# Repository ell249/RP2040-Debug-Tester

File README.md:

## RP2040 Debug Tester
### Licence and design:
-	RP2040 Debug Tester adapted by Elliot Alfirevich http://ell-tech.com/ 
-	Based on Adafruit RP2040 Tester Brains https://github.com/adafruit/RP2040-Based-Tester-Brains-PCB by Adafruit (ladyada & evaherrada) 
-	Licenced under Creative Commons Attribution-ShareAlike 3.0 Unported
-	4-layer impedance controlled circuit board, JLC04161H-7628 to ensure appropriate trace impedance for USB.

### Added features:
1.	USB-Serial converter CP2102N added to snoop serial UART bus, and allow direct serial programming of devices on test using the changeover DPDT switches.
2.	USB Hub with device power reset buttons and USB device current measurement at JP7 using Nordic PPK2 or similar. 
3.	Extra power supply functions added in the FPC 18-pin and external device 0.1in header as JP6.
4.	Additionally JP5 provides connection point for a Nordic PPK2 or similar for measuring load current of external prog-cable devices. “TEST” pin provides opportunity for custom voltages/measured currents. 
5.	Nordic PPK2 can be permanently mounted via the mounting holes and standoffs.

### Notes/changes to Adafruit design:
1.	Dedicated 3.3V regulator provided, in lieu of using the in-built RP2040 buck-boost converter. 
2.	Diode included on 3.3V supply to RP2040 VSYS to prevent back-feeding of ~5V onto the 3.3V bus from plugging in the RP2040 USB port.
3.	USB-C PD controller STUSB4500LQTR ensures enough VBUS current is provided by the host. Previously used 5.1k CC resistor method – but strictly compliant USB hosts would limit supply to 500mA which was not enough.
4.	RTS/DTR logic transistors added for ESP boot/reset to be generated from the CP2102N.
5.	High side switch (Option 1) or separate regulator (Option 2) required to power CP2102N because the CP2102N defaults to pull-up on USB data lines, causing the USB hub to disable the port at start-up (doh!)
6.	USB Hub USB2514B added to enable one cable to the host computer. 
   1.	Port 1 – CP2102N USB-Serial converter
   2.	Port 2 – USB port inc. 1.5A charging
   3.	Port 3 – USB port inc. 500mA power measurement via jumper JP7
   4.	Port 4 – RP2040 via test points.
7.	USB Hub controller strapped to report Port 1 as “non-removable” and enable USB charging support on Port 2.
8.	USB Hub controller requires an external crystal and 1M resistor. Check as newer QFN packages don’t require this resistor.
9.	SD card changed due to part availability. Note new part changes card detect from NO to NC which requires change in Brains library code.
10.	TFT connection not tested. Directly copied from original design.

### Original Adafruit Design
Forked from https://github.com/adafruit/RP2040-Based-Tester-Brains-PCB

This board is what we use internally at Adafruit to program and test boards with microcontrollers on them. 
   * An [RP2040 Pico](https://www.adafruit.com/product/5525) (or perhaps PicoW?) is used to run the test software
   * [Use a 16x2 LCD (ideally RGB backlight)](https://www.adafruit.com/product/398) for display output with color feedback such as green for pass, red for fail. RGB backlight is WS2811-controlled. Don't forget to set the contrast pot on first usage.
   * Serial1 hardware UART has RX/TX pin switch to flip directions
   * 1.9" TFT connector is placed but hasn't been tested or used yet
   * Piezo buzzer can be used for audible feedback alerts
   * STEMMA QT I2C port
   * Big reset button
   * Firmware files can be stored on MicroSD card which is slotted in. 
   * Connect the right hand side, either the 0.1" header or 18-pin EYESPI-like FPC connector to the device-under-test jig which can be different for each product. 
   * [USB Host testing is done with bitbang PIO support in TinyUSB](https://github.com/adafruit/Adafruit_TinyUSB_Arduino), USB 5V power can be turned on / off 
   * Use Philhower RP2040 core for programming
   * The RP2040 brains can perform ESP32 programming, RP2040-via-USB, AVR ICSP/UPDI, or SWD DAP. [See the TestBed library for some examples.](https://github.com/adafruit/Adafruit_TestBed)

### License

Originally designed by Limor Fried/Ladyada for Adafruit Industries. Adafruit invests time and resources providing this open source design, please support Adafruit and open-source hardware by purchasing products from [Adafruit](https://www.adafruit.com)!

Creative Commons Attribution/Share-Alike, all text above must be included in any redistribution. 
See license.txt for additional details.

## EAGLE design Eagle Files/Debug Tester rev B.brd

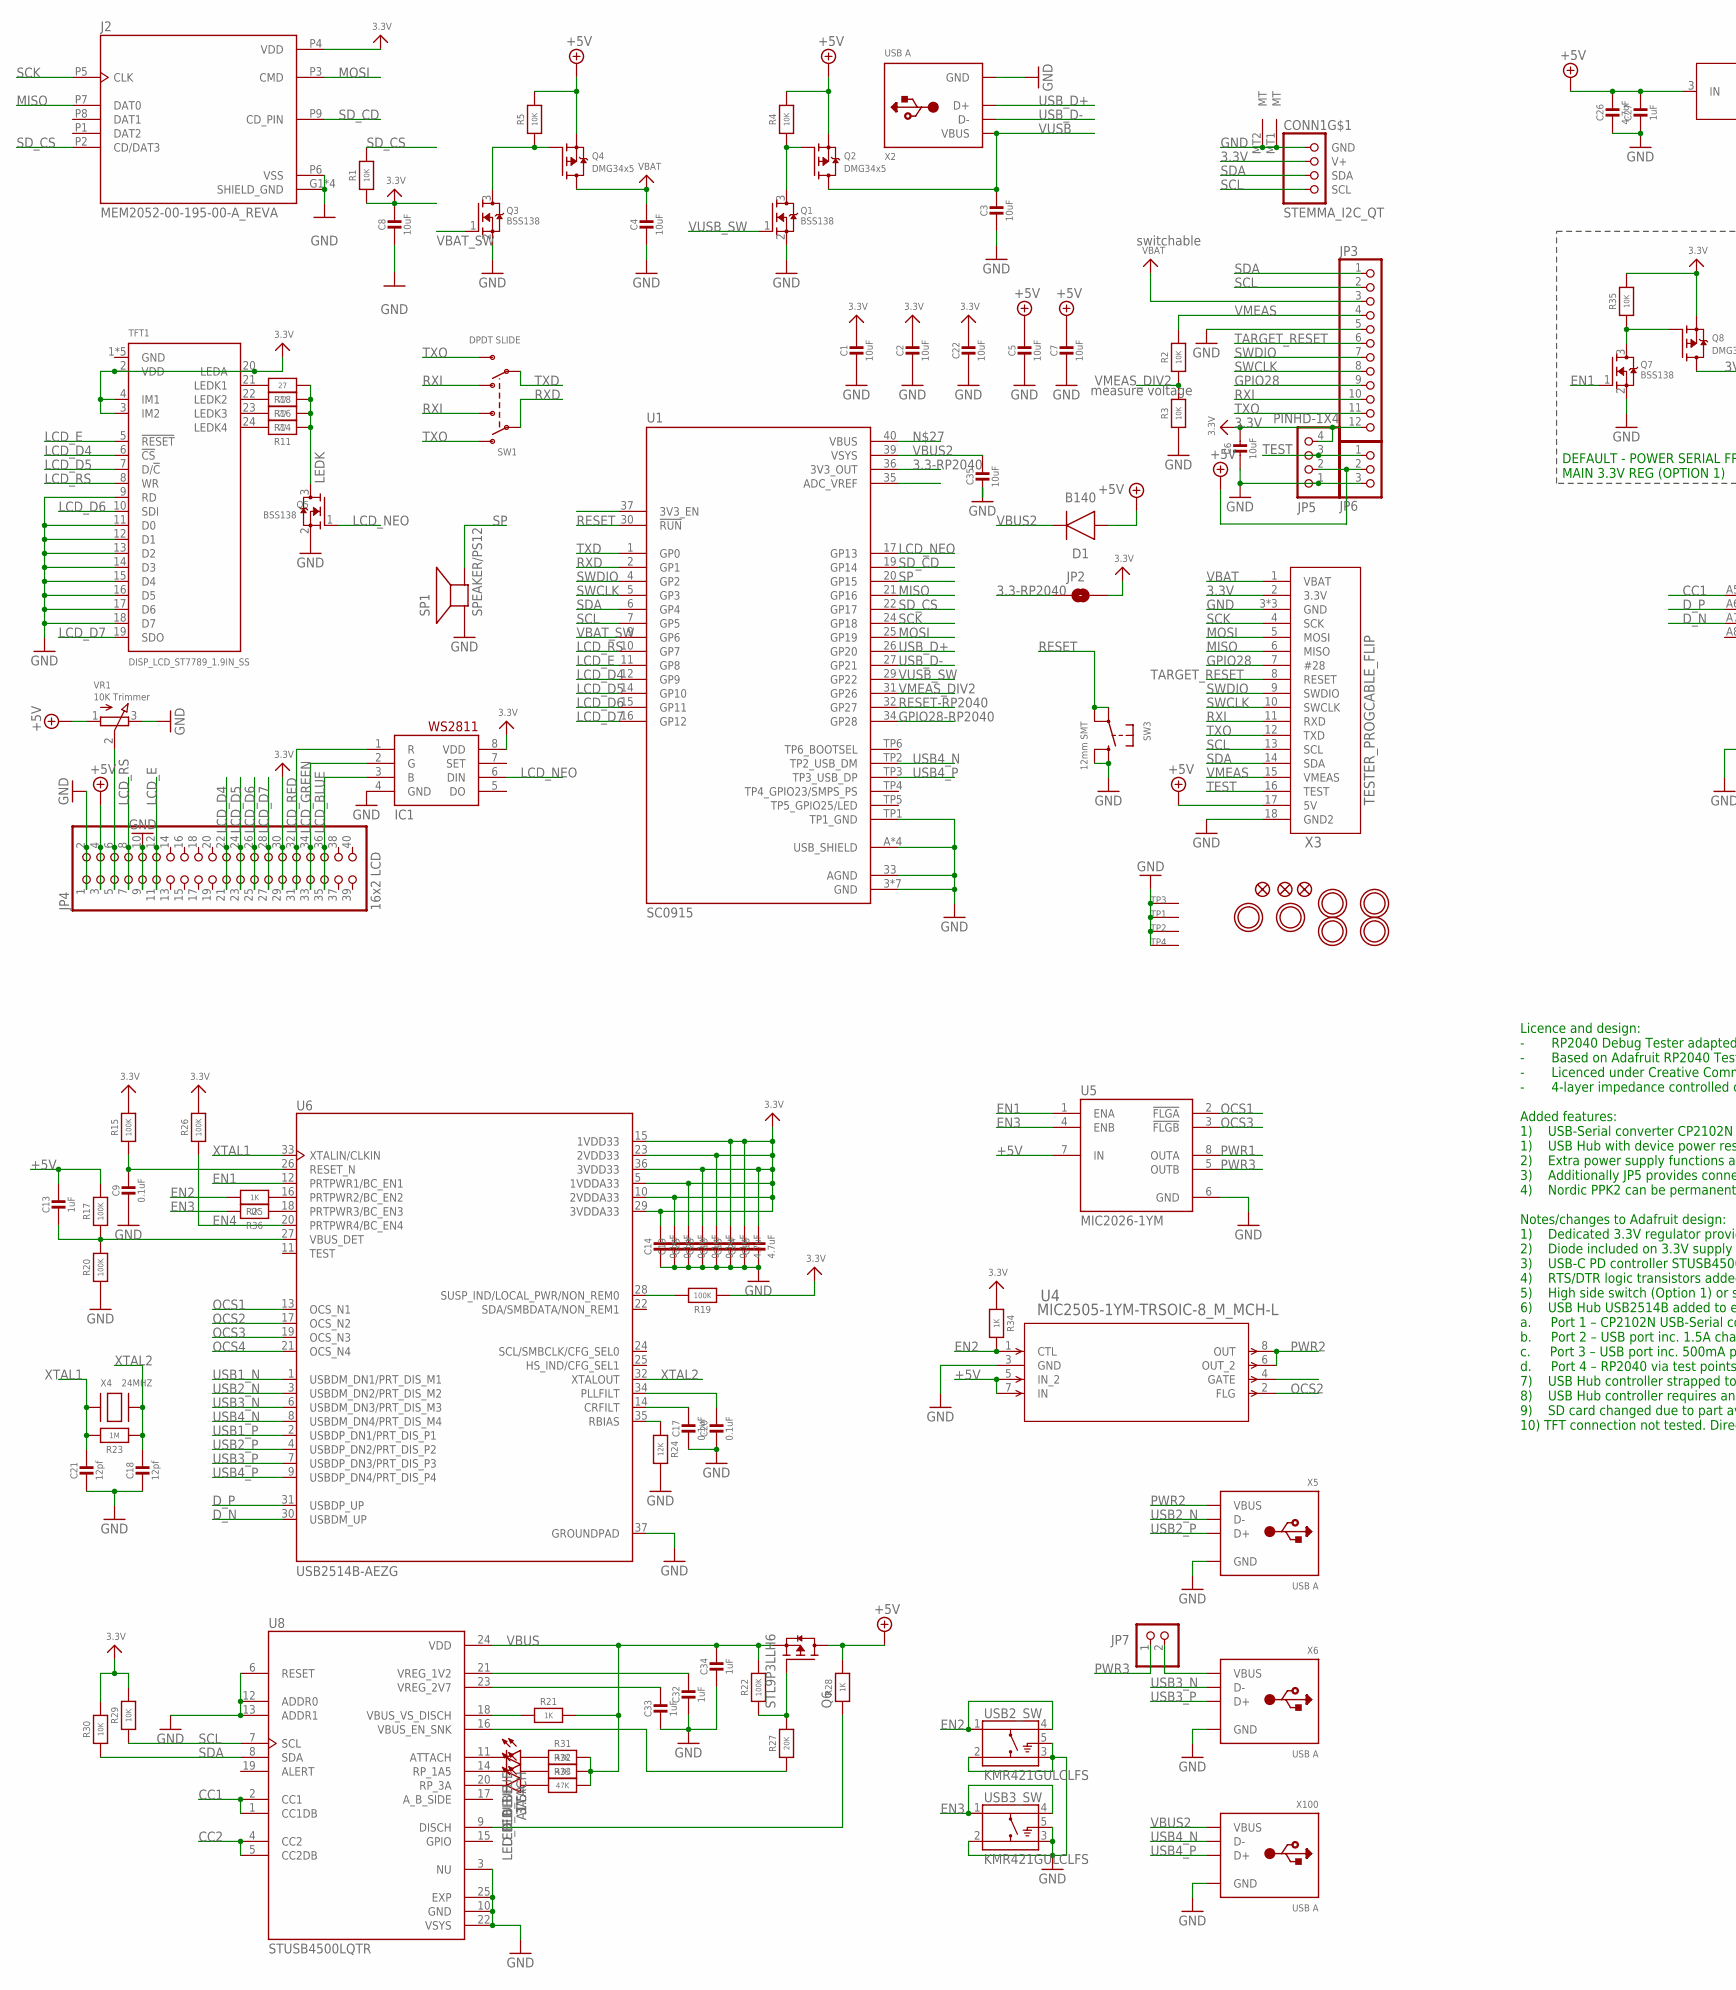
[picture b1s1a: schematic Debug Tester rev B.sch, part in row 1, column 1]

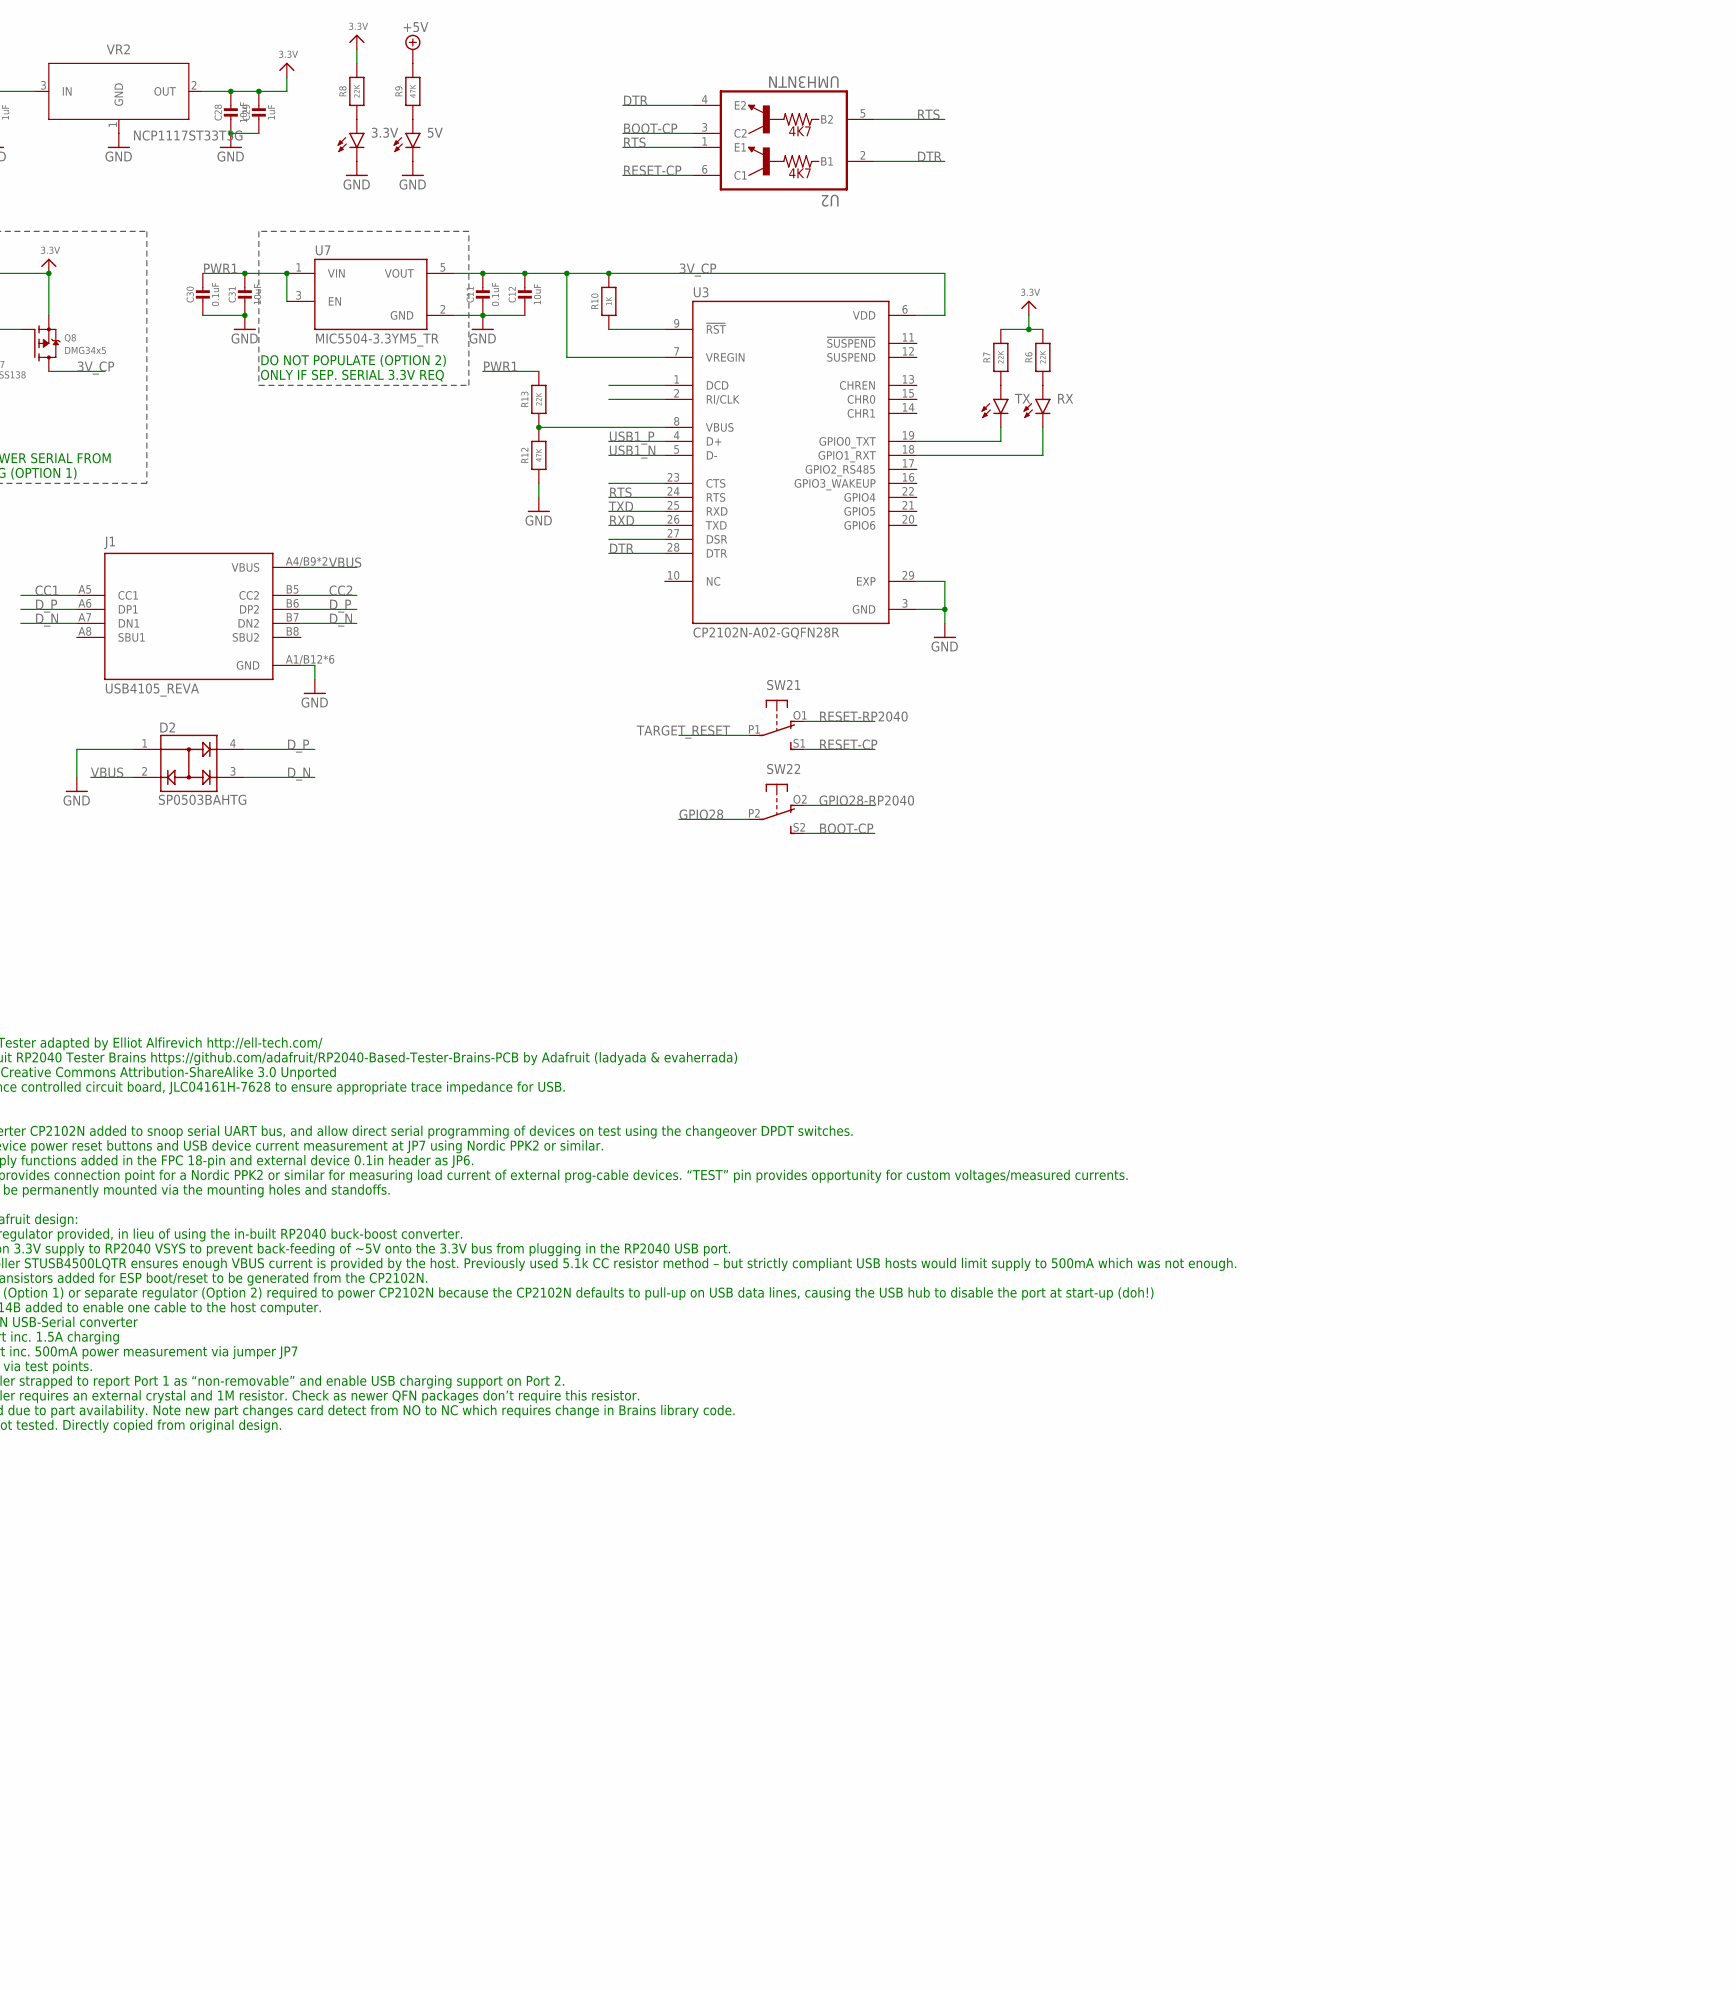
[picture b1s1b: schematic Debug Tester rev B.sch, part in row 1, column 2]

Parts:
1.5A, 3.3V, 3A, 5V: LED_BLUE; LEDC1608X55N_FLAT-B
$$U$1, $$U$2, $$U$3, $$U$5, $$U$6: MOUNTINGHOLE3.0THIN; MOUNTINGHOLE_3.0_PLATEDTHIN
ATTACH: LED_BLUE; LEDC1608X55N_FLAT-B
C1, C2, C3, C4, C5, C6, C7, C8, C12, C22, C28, C31, C35: 10uF; 0603-NO
C9, C10, C11, C14, C15, C17, C19, C20, C23, C25, C30: 0.1uF; 0603-NO
C13, C27, C29, C32, C33, C34: 1uF; 0603-NO
C16, C24, C26: 4.7uF; 0603-NO
C18, C21: 12pf; 0603-NO
CONN1: STEMMA_I2C_QT; JST_SH4
D1: B140; DIOM5226X290N
D2: SP0503BAHTG; SOT143
FID1, FID2, FID3: FIDUCIAL_1MM
IC1: WS2811-SOP8; SO08-SKINNYPADS
J1: USB4105_REVA; GCT_USB4105_REVA
J2: MEM2052-00-195-00-A_REVA; GCT_MEM2052-00-195-00-A_REVA
JP2: JUMPER-SMT_2_NC_PASTE_NO-SILK; SMT-JUMPER_2_NO_NO-SILK
JP3: HEADER-1X12OVAL; 1X12_OVAL
JP4: 16x2 LCD; 2X20_SMT_MALE
JP5: PINHD-1X4; 1X04
JP6: PINHD-1X3/90; 1X03/90
JP7: PINHD-1X2; 1X02
Q1, Q3, Q5, Q7: BSS138; SOT23-WIDE
Q2, Q4, Q8: DMG34x5; SOT23-WIDE
Q6: STL9P3LLH6; TRANS_STL9P3LLH6
R1, R2, R3, R4, R5, R29, R30, R35: 10K; 0603-NO
R6, R7, R8, R13: 22K; 0603-NO
R9, R12, R31, R32, R33: 47K; 0603-NO
R10, R21, R25, R28, R34, R36: 1K; 0603-NO
R11, R14, R16, R18: 27; 0603-NO; LCSC C25190
R15, R17, R19, R20, R22, R26: 100K; 0603-NO
R23: 1M; 0603-NO
R24: 12K; 0603-NO
R27: 20K; 0603-NO
RX: LED_BLUE; LEDC1608X55N_FLAT-B
SP1: SPEAKER/PS12; PS12
SW1: DPDT SLIDE; EG1390; LCSC C318999
SW2: DPDT-EG1390; EG1390
SW3: 12mm SMT; B3F-40XX-SMT
TFT1: DISP_LCD_ST7789_1.9IN_SS; TFT_1.9IN_170X320_30P_SS
TP1, TP2, TP3, TP4: SEWTAP_SMTNUTM3; SMT_NUT_3MM
TX: LED_BLUE; LEDC1608X55N_FLAT-B
U1: SC0915; MODULE_SC0915
U2: UMH3NTN; SOP65P210X100-6N
U3: CP2102N-A02-GQFN28R; IC_CP2102N-A02-GQFN28R
U4: MIC2505-1YM-TRSOIC-8_M_MCH-L; SOIC-8_M_MCH-L
U5: MIC2026-1YM; SOIC127P599X173-8N
U6: USB2514B-AEZG; VQFN50P600X600X100-36N
U7: MIC5504-3.3YM5_TR; SOT95P280X145-5N
U8: STUSB4500LQTR; QFN50P400X400X100-25N
U$7: MOUNTINGHOLE3.0THIN; MOUNTINGHOLE_3.0_PLATEDTHIN
USB2_SW, USB3_SW: KMR421GULCLFS; SW_KMR421GULCLFS
VR1: 10K Trimmer; TRIMPOT_BOURNS_TC33X-2
VR2: NCP1117ST33T3G; SOT230P700X170-4
X2, X5, X6, X100: USB A; USB_HOST-SMT
X3: TESTER_PROGCABLE_FLIP; FPC_0.5MM_18PIN
X4: 24MHZ; NX5032

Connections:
3.3-RP2040: JP2.1, U1.36 (3V3_OUT)
3.3V: C1.1, C2.1, C6.1, C8.1, C10.1, C14.1, C15.1, C16.1, C19.1, C22.1, C23.1, C24.1, C25.1, C28.1, C29.1, CONN1.2 (V+), IC1.8 (VDD), J2.P4 (VDD), JP2.2, JP3.12, JP4.29, JP4.30, JP5.4, Q8.2 (S), R1.1, R6.2, R7.2, R8.2, R15.2, R19.1, R26.2, R29.2, R30.2, R34.1, R35.2, TFT1.2 (VDD), TFT1.3 (IM2), TFT1.4 (IM1), TFT1.20 (LEDA), U6.5 (1VDDA33), U6.10 (2VDDA33), U6.15 (1VDD33), U6.23 (2VDD33), U6.29 (3VDDA33), U6.36 (3VDD33), VR2.2 (OUT), X3.2 (3.3V)
3V_CP: C11.1, C12.1, Q8.3 (D), R10.2, U3.6 (VDD), U3.7 (VREGIN), U7.5 (VOUT)
!VBAT_SW1: Q3.3 (D), Q4.1 (G), R5.1
!VBAT_SW2: Q1.3 (D), Q2.1 (G), R4.1
+5V: C5.1, C7.1, C13.1, C26.1, C27.1, D1.2 (A), JP4.3, JP4.4, JP5.2, JP6.2, Q2.2 (S), Q4.2 (S), Q6.5 (D), Q6.5_1 (D), Q6.5_2 (D), R4.2, R5.2, R9.2, R17.2, R28.2, U4.5 (IN_2), U4.7 (IN), U5.7 (IN), VR1.1 (A), VR2.3 (IN), X3.17 (5V)
BOOT-CP: SW2.S2 (S), U2.3 (C2)
CC1: J1.A5 (CC1), U8.1 (CC1DB), U8.2 (CC1)
CC2: J1.B5 (CC2), U8.4 (CC2), U8.5 (CC2DB)
DTR: U2.2 (B1), U2.4 (E2), U3.28 (DTR)
D_N: D2.3, J1.A7 (DN1), J1.B7 (DN2), U6.30 (USBDM_UP)
D_P: D2.4, J1.A6 (DP1), J1.B6 (DP2), U6.31 (USBDP_UP)
EN1: Q7.1 (G), U5.1 (ENA), U6.12 (PRTPWR1/BC_EN1)
EN2: R25.2, R34.2, U4.1 (CTL), USB2_SW.1, USB2_SW.4
EN3: R36.2, U5.4 (ENB), USB3_SW.1, USB3_SW.4
EN4: R26.1, U6.20 (PRTPWR4/BC_EN4)
GND: 3.3V.C, 5V.C, C1.2, C2.2, C3.2, C4.2, C5.2, C6.2, C7.2, C8.2, C9.2, C10.2, C11.2, C12.2, C14.2, C15.2, C16.2, C17.2, C18.2, C19.2, C20.2, C21.2, C22.2, C23.2, C24.2, C25.2, C26.2, C27.2, C28.2, C29.2, C30.2, C31.2, C32.2, C33.2, C34.2, C35.2, CONN1.1 (GND), CONN1.MT1 (MT), CONN1.MT2 (MT), D2.1, IC1.4 (GND), J1.A1/B12 (GND), J1.B1/A12 (GND), J1.G1 (GND), J1.G2 (GND), J1.G3 (GND), J1.G4 (GND), J2.G1 (SHIELD_GND), J2.G2 (SHIELD_GND), J2.G3 (SHIELD_GND), J2.G4 (SHIELD_GND), J2.P6 (VSS), JP3.5, JP4.1, JP4.2, JP4.9, JP4.10, JP5.1, JP6.3, Q1.2 (S), Q3.2 (S), Q5.2 (S), Q7.2 (S), R3.1, R12.1, R20.1, R24.2, SP1.P$1 (+), SW3.P$3 (S), SW3.P$4 (S1), TFT1.1 (GND), TFT1.9 (RD), TFT1.11 (D0), TFT1.12 (D1), TFT1.13 (D2), TFT1.14 (D3), TFT1.15 (D4), TFT1.16 (D5), TFT1.17 (D6), TFT1.18 (D7), TFT1.25 (GND), TFT1.30 (GND), TFT1.MNT1 (GND), TFT1.MNT2 (GND), TP1.P$1, TP2.P$1, TP3.P$1, TP4.P$1, U1.3 (GND), U1.8 (GND), U1.13 (GND), U1.18 (GND), U1.23 (GND), U1.28 (GND), U1.33 (AGND), U1.38 (GND), U1.A (USB_SHIELD), U1.B (USB_SHIELD), U1.C (USB_SHIELD), U1.D (USB_SHIELD), U1.TP1 (TP1_GND), U3.3 (GND), U3.29 (EXP), U4.3 (GND), U5.6 (GND), U6.37 (GROUNDPAD), U7.2 (GND), U8.3 (NU), U8.6 (RESET), U8.10 (GND), U8.12 (ADDR0), U8.13 (ADDR1), U8.22 (VSYS), U8.25 (EXP), USB2_SW.2, USB2_SW.3, USB2_SW.5 (G), USB3_SW.2, USB3_SW.3, USB3_SW.5 (G), VR1.3 (E), VR2.1 (GND), X2.GND, X3.3 (GND), X3.18 (GND2), X3.SUPPORT1 (GND), X3.SUPPORT2 (GND), X5.GND, X6.GND, X100.GND
GPIO28: JP3.9, SW2.P2, X3.7 (#28)
GPIO28-RP2040: SW2.O2 (O), U1.34 (GP28)
LCD_BLUE: IC1.3 (B), JP4.35, JP4.36
LCD_D4: JP4.21, JP4.22, TFT1.6 (!CS), U1.12 (GP9)
LCD_D5: JP4.23, JP4.24, TFT1.7 (D/!C), U1.14 (GP10)
LCD_D6: JP4.25, JP4.26, TFT1.10 (SDI), U1.15 (GP11)
LCD_D7: JP4.27, JP4.28, TFT1.19 (SDO), U1.16 (GP12)
LCD_E: JP4.11, JP4.12, TFT1.5 (!RESET), U1.11 (GP8)
LCD_GREEN: IC1.2 (G), JP4.33, JP4.34
LCD_NEO: IC1.6 (DIN), Q5.1 (G), U1.17 (GP13)
LCD_RED: IC1.1 (R), JP4.31, JP4.32
LCD_RS: JP4.7, JP4.8, TFT1.8 (WR), U1.10 (GP7)
LEDK: Q5.3 (D), R11.1, R14.1, R16.1, R18.1
MISO: J2.P7 (DAT0), U1.21 (GP16), X3.6 (MISO)
MOSI: J2.P3 (CMD), U1.25 (GP19), X3.5 (MOSI)
unnamed: R25.1, U6.16 (PRTPWR2/BC_EN2)
unnamed: R18.2, TFT1.21 (LEDK1)
unnamed: R16.2, TFT1.22 (LEDK2)
unnamed: R14.2, TFT1.23 (LEDK3)
unnamed: R11.2, TFT1.24 (LEDK4)
unnamed: JP4.5, JP4.6, VR1.2 (S)
unnamed: R10.1, U3.9 (!RST)
unnamed: C13.2, R17.1, R20.2, U6.27 (VBUS_DET)
unnamed: R12.2, R13.1, U3.8 (VBUS)
unnamed: TX.C, U3.19 (GPIO0_TXT)
unnamed: RX.C, U3.18 (GPIO1_RXT)
unnamed: R7.1, TX.A
unnamed: R6.1, RX.A
unnamed: C9.1, R15.1, U6.26 (RESET_N)
unnamed: C17.1, U6.14 (CRFILT)
unnamed: C20.1, U6.34 (PLLFILT)
unnamed: ATTACH.C, U8.11 (ATTACH)
unnamed: C33.1, U8.23 (VREG_2V7)
unnamed: R24.1, U6.35 (RBIAS)
unnamed: R19.2, U6.28 (SUSP_IND/LOCAL_PWR/NON_REM0)
unnamed: C32.1, U8.21 (VREG_1V2)
unnamed: R36.1, U6.18 (PRTPWR3/BC_EN3)
unnamed: 1.5A.C, U8.14 (RP_1A5)
unnamed: R21.1, U8.18 (VBUS_VS_DISCH)
unnamed: Q6.4 (G), R22.1, R27.2
unnamed: 3.3V.A, R8.1
unnamed: 5V.A, R9.1
unnamed: JP7.2, X6.VBUS
unnamed: 3A.C, U8.20 (RP_3A)
unnamed: R28.1, U8.9 (DISCH)
unnamed: R27.1, U8.16 (VBUS_EN_SNK)
unnamed: ATTACH.A, R31.1
unnamed: 1.5A.A, R32.1
unnamed: 3A.A, R33.1
unnamed: Q7.3 (D), Q8.1 (G), R35.1
OCS1: U5.2 (!FLGA), U6.13 (OCS_N1)
OCS2: U4.2 (FLG), U6.17 (OCS_N2)
OCS3: U5.3 (!FLGB), U6.19 (OCS_N3)
OCS4: U6.21 (OCS_N4)
PWR1: C30.1, C31.1, R13.2, U5.8 (OUTA), U7.1 (VIN), U7.3 (EN)
PWR2: U4.6 (OUT_2), U4.8 (OUT), X5.VBUS
PWR3: JP7.1, U5.5 (OUTB)
RESET: SW3.P$1, SW3.P$2 (P1), U1.30 (!RUN)
RESET-CP: SW2.S1 (S), U2.6 (C1)
RESET-RP2040: SW2.O1 (O), U1.32 (GP27)
RTS: U2.1 (E1), U2.5 (B2), U3.24 (RTS)
RXD: SW1.P1, U1.2 (GP1), U3.26 (TXD)
RXI: JP3.10, SW1.O2, SW1.S1, X3.11 (RXD)
SCK: J2.P5 (CLK), U1.24 (GP18), X3.4 (SCK)
SCL: CONN1.4 (SCL), JP3.2, R29.1, U1.7 (GP5), U8.7 (SCL), X3.13 (SCL)
SDA: CONN1.3 (SDA), JP3.1, R30.1, U1.6 (GP4), U8.8 (SDA), X3.14 (SDA)
SD_CD: J2.P9 (CD_PIN), U1.19 (GP14)
SD_CS: J2.P2 (CD/DAT3), R1.2, U1.22 (GP17)
SP: SP1.P$2 (-), U1.20 (GP15)
SWCLK: JP3.8, U1.5 (GP3), X3.10 (SWCLK)
SWDIO: JP3.7, U1.4 (GP2), X3.9 (SWDIO)
TARGET_RESET: JP3.6, SW2.P1, X3.8 (RESET)
TEST: JP5.3, JP6.1, X3.16 (TEST)
TXD: SW1.P2, U1.1 (GP0), U3.25 (RXD)
TXO: JP3.11, SW1.O1, SW1.S2, X3.12 (TXD)
USB1_N: U3.5 (D-), U6.1 (USBDM_DN1/PRT_DIS_M1)
USB1_P: U3.4 (D+), U6.2 (USBDP_DN1/PRT_DIS_P1)
USB2_N: U6.3 (USBDM_DN2/PRT_DIS_M2), X5.D-
USB2_P: U6.4 (USBDP_DN2/PRT_DIS_P2), X5.D+
USB3_N: U6.6 (USBDM_DN3/PRT_DIS_M3), X6.D-
USB3_P: U6.7 (USBDP_DN3/PRT_DIS_P3), X6.D+
USB4_N: U1.TP2 (TP2_USB_DM), U6.8 (USBDM_DN4/PRT_DIS_M4), X100.D-
USB4_P: U1.TP3 (TP3_USB_DP), U6.9 (USBDP_DN4/PRT_DIS_P4), X100.D+
USB_D+: U1.26 (GP20), X2.D+
USB_D-: U1.27 (GP21), X2.D-
VBAT: C4.1, JP3.3, Q4.3 (D), X3.1 (VBAT)
VBAT_SW: Q3.1 (G), U1.9 (GP6)
VBUS: C34.1, D2.2, J1.A4/B9 (VBUS), J1.B4/A9 (VBUS), Q6.1 (S), Q6.2 (S), Q6.3 (S), R21.2, R22.2, R31.2, R32.2, R33.2, U8.24 (VDD)
VBUS2: C35.1, D1.1 (C), U1.39 (VSYS), X100.VBUS
VMEAS: JP3.4, R2.2, X3.15 (VMEAS)
VMEAS_DIV2: R2.1, R3.2, U1.31 (GP26)
VUSB: C3.1, Q2.3 (D), X2.VBUS
VUSB_SW: Q1.1 (G), U1.29 (GP22)
XTAL1: C21.1, R23.2, U6.33 (XTALIN/CLKIN), X4.P$1
XTAL2: C18.1, R23.1, U6.32 (XTALOUT), X4.P$2

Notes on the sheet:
switchable
measure voltage
DO NOT POPULATE (OPTION 2) ONLY IF SEP. SERIAL 3.3V REQ
DEFAULT - POWER SERIAL FROM MAIN 3.3V REG (OPTION 1)
Licence and design: - RP2040 Debug Tester adapted by Elliot Alfirevich http://ell-tech.com/ - Based on Adafruit RP2040 Tester Brains https://github.com/adafruit/RP2040-Based-Tester-Brains-PCB by Adafruit (ladyada & evaherrada) - Licenced under Creative Commons Attribution-ShareAlike 3.0 Unported - 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

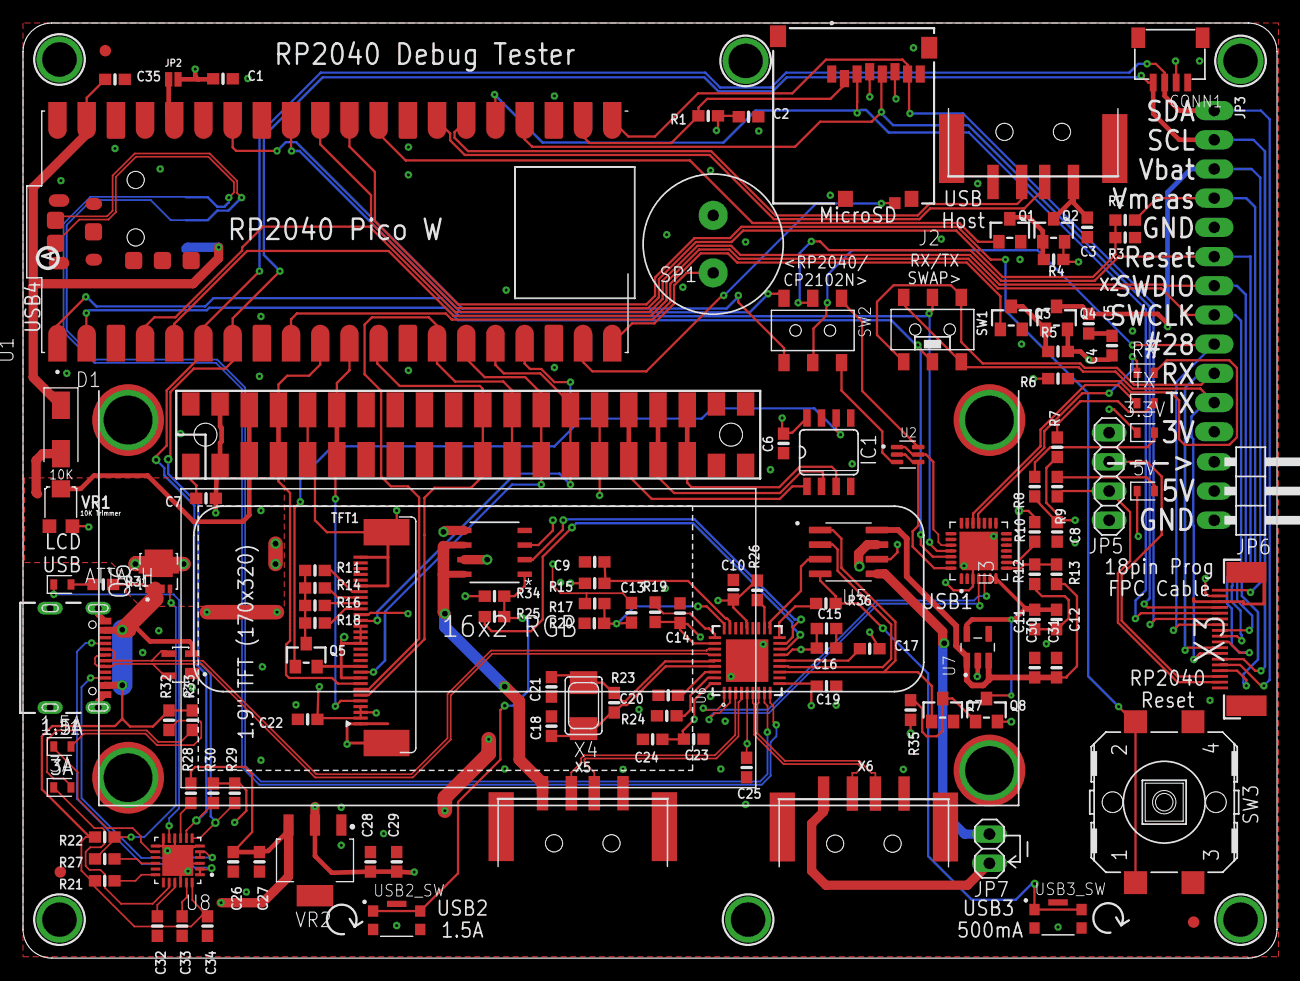
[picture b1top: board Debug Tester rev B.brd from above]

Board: 4 copper layers, 109.1 x 81.4 mm, 135 parts (1 on the bottom side), 111 nets.

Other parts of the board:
$$U$4: PCBFEAT-REV-040

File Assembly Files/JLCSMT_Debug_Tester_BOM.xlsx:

Comment | Designator | Footprint | JLCPCB Part#
LED_BLUE | 1.5A, 3.3V, 3A, 5V, ATTACH, RX, TX | LEDC1608X55N_FLAT-B | C72038
10uF | C1, C2, C3, C4, C5, C6, C7, C8, C12, C22, C28, C31, C35 | 0603-NO | C194427
1uF | C13, C27, C29, C32, C33, C34 | 0603-NO | C15849
4.7uF | C16, C24, C26 | 0603-NO | C329940
12pF | C18, C21 | 0603-NO | C182482
0.1uF | C9, C10, C11, C14, C15, C17, C19, C20, C23, C25, C30 | 0603-NO | C14663
STEMMA_I2C_QT | CONN1 | JST_SH4 | C160404
B140-13-F | D1 | DIOM5226X290N | C85098
SP0503BAHTG | D2 | SOT143 | C7074
WS2811-SOP8 | IC1 | SO08-SKINNYPADS | C114581
USB4105_REVA | J1 | GCT_USB4105_REVA | C963370
MEM2052-00-195-00-A_REVA | J2 | GCT_MEM2052-00-195-00-A_REVA | C266607
16x2 LCD | JP4 | 2X20_SMT_MALE | C2685092
BSS138 | Q1, Q3, Q5, Q7 | SOT23-WIDE | C2874697
DMG34x5 | Q2, Q4, Q8 | SOT23-WIDE | C96616
10K | R1, R2, R3, R4, R5, R29, R30, R35 | 0603-NO | C309083
1K | R10, R21, R25, R28, R34, R36 | 0603-NO | C103232
27 | R11, R14, R16, R18 | 0603-NO | C881414
100K | R15, R17, R19, R20, R22, R26 | 0603-NO | C103200
1M | R23 | 0603-NO | C217860
12K | R24 | 0603-NO | C217716
20K | R27 | 0603-NO | C163879
22K | R6, R7, R8, R13 | 0603-NO | C705918
47K | R9, R12, R31, R32, R33 | 0603-NO | C912116
DPDT SLIDE | SW1, SW2 | EG1390 | C223854
12mm SMT | SW3 | B3F-40XX-SMT | C2931098
DISP_LCD_ST7789_1.9IN_SS | TFT1 | TFT_1.9IN_170X320_30P_SS | C375905
UMH3NTN | U2 | SOP65P210X100-6N | C123008
CP2102N-A02-GQFN28R | U3 | IC_CP2102N-A02-GQFN28R | C964632
MIC2505-1YM-TRSOIC-8_M_MCH-L | U4 | SOIC-8_M_MCH-L | C627817
MIC2026-1YM | U5 | SOIC127P599X173-8N | C144190
USB2514B-AEZG | U6 | VQFN50P600X600X100-36N | C16251
KMR421GULCLFS | USB2_SW, USB3_SW | SW_KMR421GULCLFS | C99271
10K Trimmer | VR1 | TRIMPOT_BOURNS_TC33X-2 | C719176
NCP1117ST33T3G | VR2 | SOT230P700X170-4 | C444421
USB A | X2, X5, X6 | USB_HOST-SMT | C112455
TESTER_PROGCABLE_FLIP | X3 | FPC_0.5MM_18PIN | C181732
24MHZ 7pf | X4 | NX5032 | C295068

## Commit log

2023-07-11 Initial commit
    First commit of fabricated design.

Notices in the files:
Eagle Files/Debug Tester rev B.brd:
Licenced under Attribution-ShareAlike 3.0
https://creativecommons.org/licenses/by-sa/3.0
parts and their libraries:
microbuilder: This work is placed in the public domain, and may be freely used for commercial and non-commercial work with the following conditions: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
SparkFun-Jumpers: Licensing: Creative Commons ShareAlike 4.0 International - https://creativecommons.org/licenses/by-sa/4.0
